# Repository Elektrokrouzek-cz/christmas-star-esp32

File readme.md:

# Christmas star with ESP32
This is the construction of ESP32-C3 based Christmas star.

There are also code examples written in MicroPython.

PCB is 2-layer and was designed using KiCad 10. Fabrication output for JLCPCB is in 
gerber folder.

**Happy soldering!**

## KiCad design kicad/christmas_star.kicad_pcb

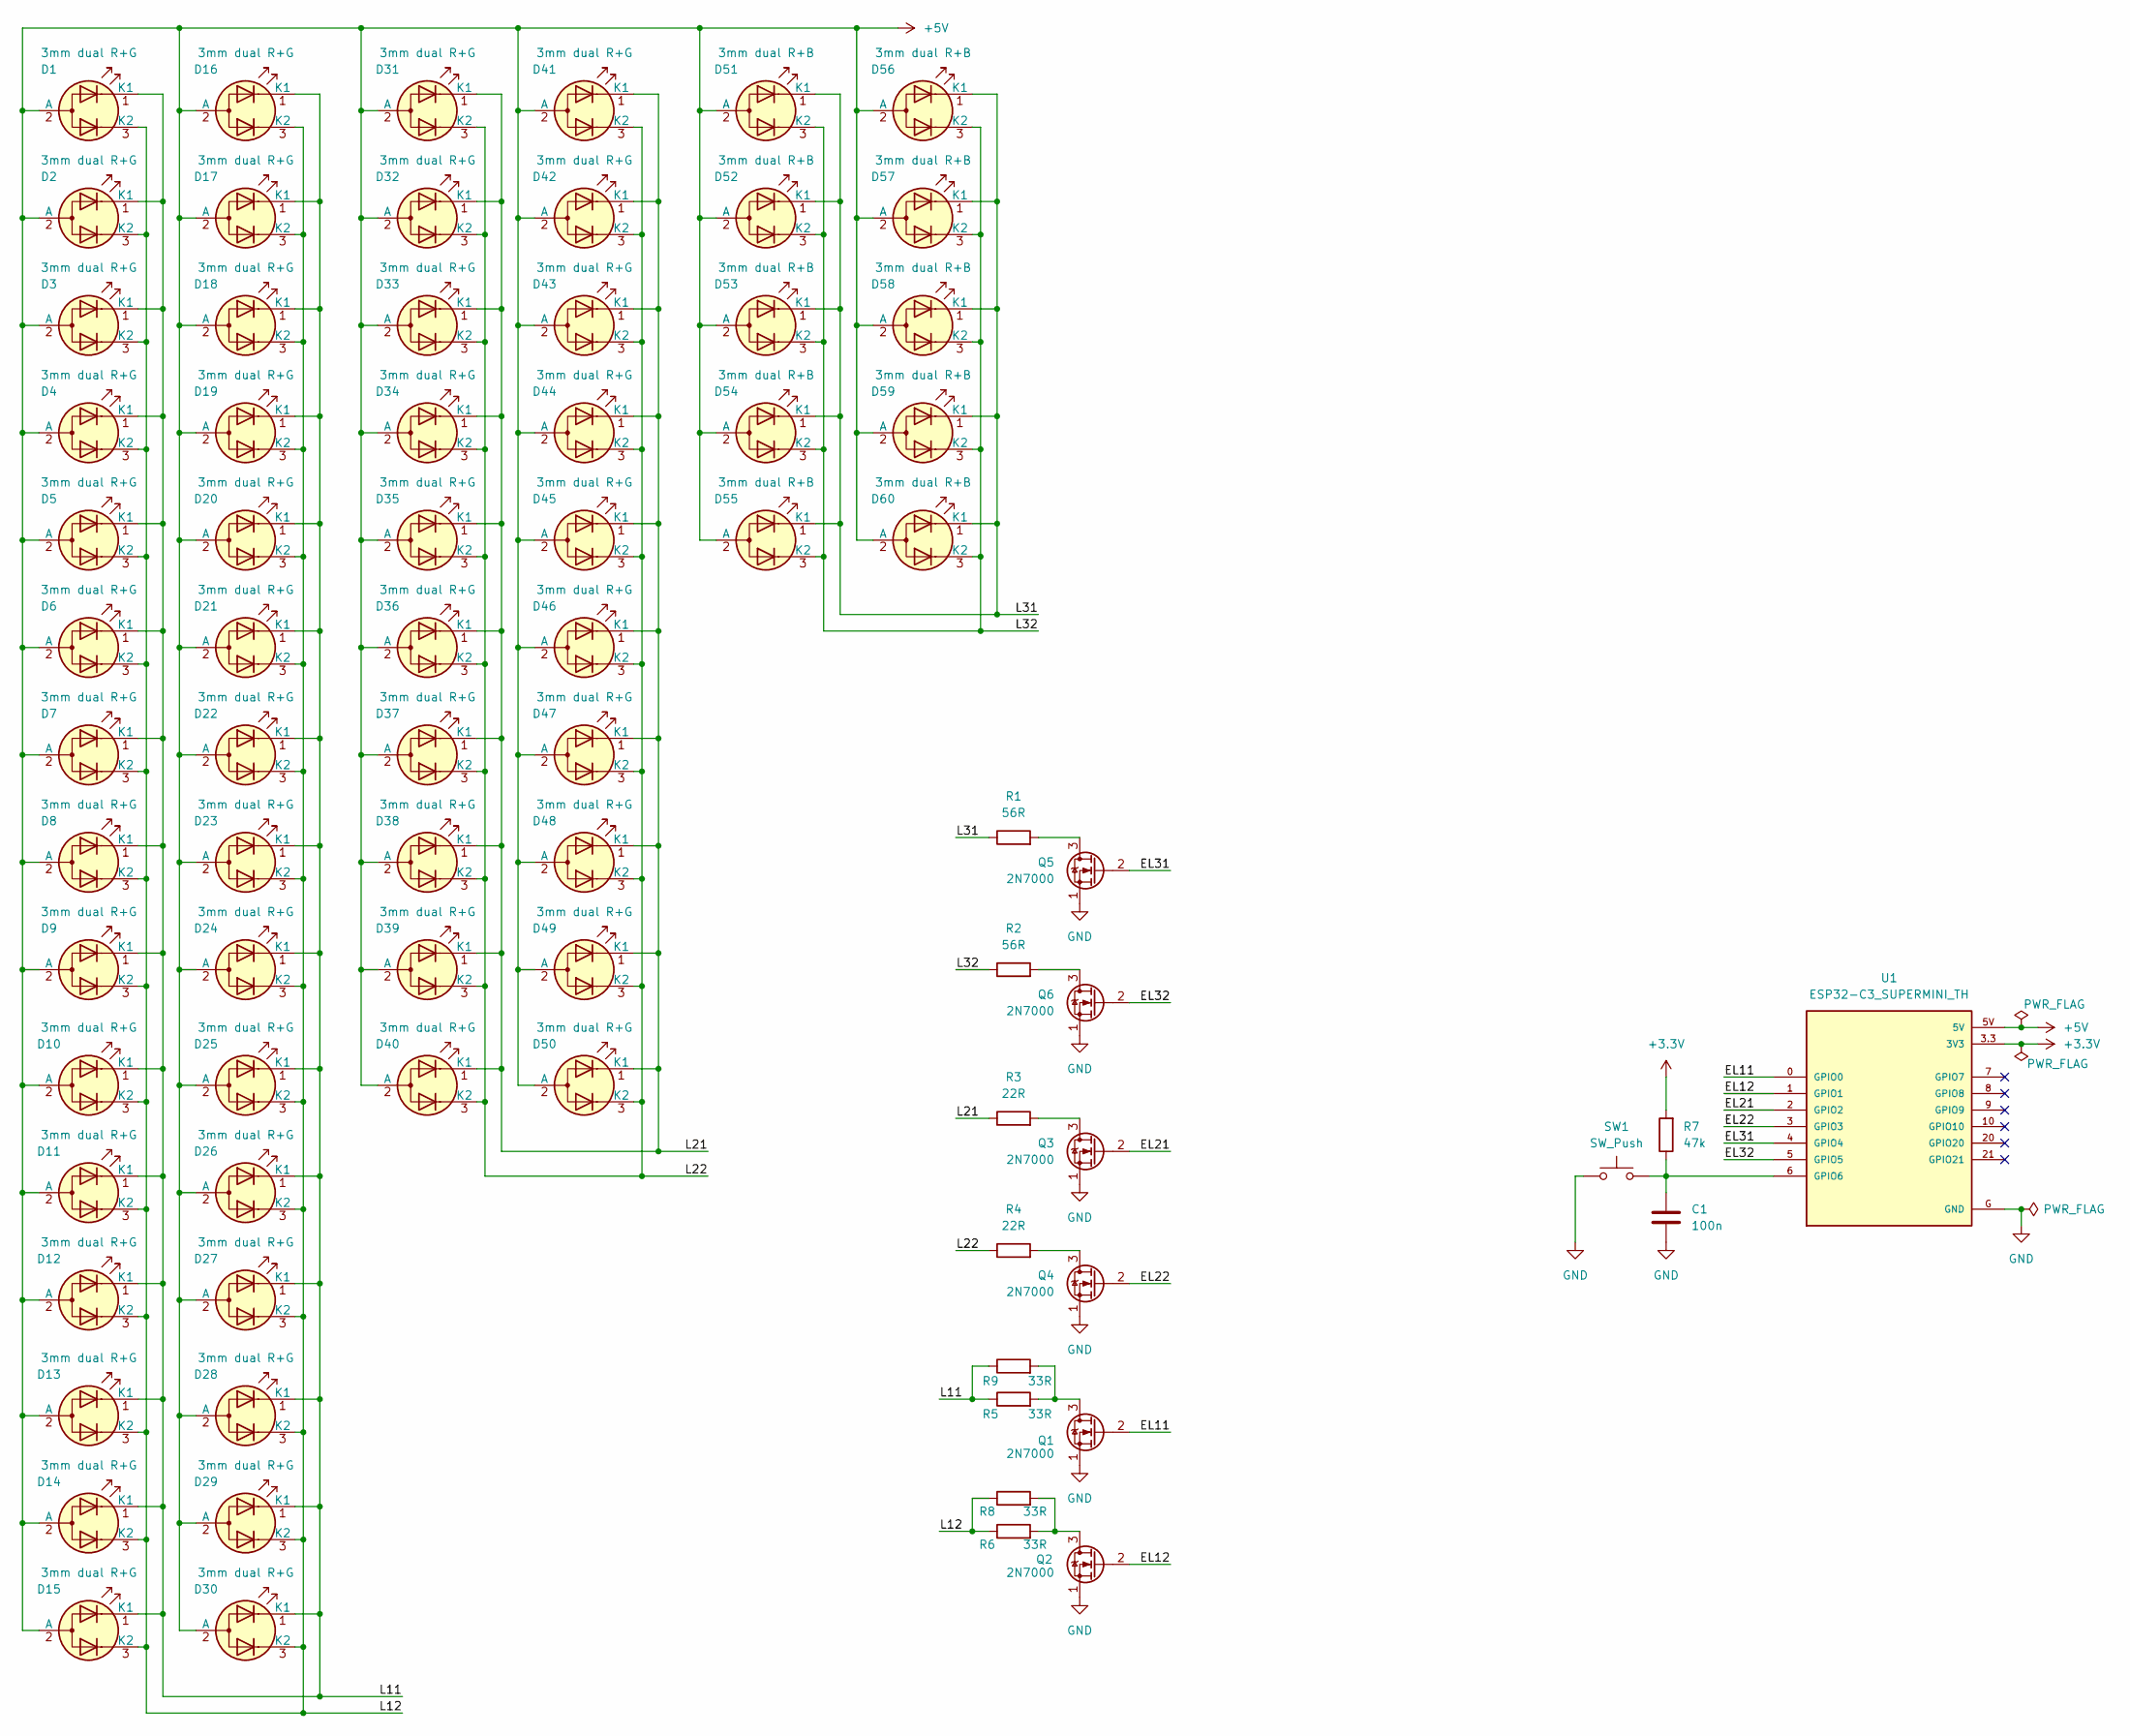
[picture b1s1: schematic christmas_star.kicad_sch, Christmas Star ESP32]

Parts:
C1: 100n; C_Disc_D5.0mm_W2.5mm_P5.00mm
D1, D2, D3, D4, D5, D6, D7, D8, D9, D10, D11, D12, D13, D14, D15, D16, D17, D18, D19, D20, D21, D22, D23, D24, D25, D26, D27, D28, D29, D30, D31, D32, D33, D34, D35, D36, D37, D38, D39, D40, D41, D42, D43, D44, D45, D46, D47, D48, D49, D50: 3mm dual R+G; LED_D3.0mm-3
D51, D52, D53, D54, D55, D56, D57, D58, D59, D60: 3mm dual R+B; LED_D3.0mm-3
Q1, Q2, Q3, Q4, Q5, Q6: 2N7000; TO-92_Inline_Wide
R1, R2: 56R; R_Axial_DIN0207_L6.3mm_D2.5mm_P7.62mm_Horizontal
R3, R4: 22R; R_Axial_DIN0207_L6.3mm_D2.5mm_P7.62mm_Horizontal
R5, R6, R8, R9: 33R; R_Axial_DIN0207_L6.3mm_D2.5mm_P7.62mm_Horizontal
R7: 47k; R_Axial_DIN0207_L6.3mm_D2.5mm_P7.62mm_Horizontal
SW1: SW_Push; SW_PUSH_6mm_H13mm
U1: ESP32-C3_SUPERMINI_TH; MODULE_ESP32-C3_SUPERMINI

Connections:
+3.3V: R7.2, U1.3.3 (3V3)
+5V: D1.2 (A), D2.2 (A), D3.2 (A), D4.2 (A), D5.2 (A), D6.2 (A), D7.2 (A), D8.2 (A), D9.2 (A), D10.2 (A), D11.2 (A), D12.2 (A), D13.2 (A), D14.2 (A), D15.2 (A), D16.2 (A), D17.2 (A), D18.2 (A), D19.2 (A), D20.2 (A), D21.2 (A), D22.2 (A), D23.2 (A), D24.2 (A), D25.2 (A), D26.2 (A), D27.2 (A), D28.2 (A), D29.2 (A), D30.2 (A), D31.2 (A), D32.2 (A), D33.2 (A), D34.2 (A), D35.2 (A), D36.2 (A), D37.2 (A), D38.2 (A), D39.2 (A), D40.2 (A), D41.2 (A), D42.2 (A), D43.2 (A), D44.2 (A), D45.2 (A), D46.2 (A), D47.2 (A), D48.2 (A), D49.2 (A), D50.2 (A), D51.2 (A), D52.2 (A), D53.2 (A), D54.2 (A), D55.2 (A), D56.2 (A), D57.2 (A), D58.2 (A), D59.2 (A), D60.2 (A), U1.5V
/EL11: Q1.2 (G), U1.0 (GPIO0)
/EL12: Q2.2 (G), U1.1 (GPIO1)
/EL21: Q3.2 (G), U1.2 (GPIO2)
/EL22: Q4.2 (G), U1.3 (GPIO3)
/EL31: Q5.2 (G), U1.4 (GPIO4)
/EL32: Q6.2 (G), U1.5 (GPIO5)
/L11: D1.1 (K1), D2.1 (K1), D3.1 (K1), D4.1 (K1), D5.1 (K1), D6.1 (K1), D7.1 (K1), D8.1 (K1), D9.1 (K1), D10.1 (K1), D11.1 (K1), D12.1 (K1), D13.1 (K1), D14.1 (K1), D15.1 (K1), D16.1 (K1), D17.1 (K1), D18.1 (K1), D19.1 (K1), D20.1 (K1), D21.1 (K1), D22.1 (K1), D23.1 (K1), D24.1 (K1), D25.1 (K1), D26.1 (K1), D27.1 (K1), D28.1 (K1), D29.1 (K1), D30.1 (K1), R5.1, R9.1
/L12: D1.3 (K2), D2.3 (K2), D3.3 (K2), D4.3 (K2), D5.3 (K2), D6.3 (K2), D7.3 (K2), D8.3 (K2), D9.3 (K2), D10.3 (K2), D11.3 (K2), D12.3 (K2), D13.3 (K2), D14.3 (K2), D15.3 (K2), D16.3 (K2), D17.3 (K2), D18.3 (K2), D19.3 (K2), D20.3 (K2), D21.3 (K2), D22.3 (K2), D23.3 (K2), D24.3 (K2), D25.3 (K2), D26.3 (K2), D27.3 (K2), D28.3 (K2), D29.3 (K2), D30.3 (K2), R6.1, R8.1
/L21: D31.1 (K1), D32.1 (K1), D33.1 (K1), D34.1 (K1), D35.1 (K1), D36.1 (K1), D37.1 (K1), D38.1 (K1), D39.1 (K1), D40.1 (K1), D41.1 (K1), D42.1 (K1), D43.1 (K1), D44.1 (K1), D45.1 (K1), D46.1 (K1), D47.1 (K1), D48.1 (K1), D49.1 (K1), D50.1 (K1), R3.1
/L22: D31.3 (K2), D32.3 (K2), D33.3 (K2), D34.3 (K2), D35.3 (K2), D36.3 (K2), D37.3 (K2), D38.3 (K2), D39.3 (K2), D40.3 (K2), D41.3 (K2), D42.3 (K2), D43.3 (K2), D44.3 (K2), D45.3 (K2), D46.3 (K2), D47.3 (K2), D48.3 (K2), D49.3 (K2), D50.3 (K2), R4.1
/L31: D51.1 (K1), D52.1 (K1), D53.1 (K1), D54.1 (K1), D55.1 (K1), D56.1 (K1), D57.1 (K1), D58.1 (K1), D59.1 (K1), D60.1 (K1), R1.1
/L32: D51.3 (K2), D52.3 (K2), D53.3 (K2), D54.3 (K2), D55.3 (K2), D56.3 (K2), D57.3 (K2), D58.3 (K2), D59.3 (K2), D60.3 (K2), R2.1
GND: C1.2, Q1.1 (S), Q2.1 (S), Q3.1 (S), Q4.1 (S), Q5.1 (S), Q6.1 (S), SW1.1, U1.G (GND)
unnamed: Q1.3 (D), R5.2, R9.2
unnamed: Q2.3 (D), R6.2, R8.2
unnamed: Q3.3 (D), R3.2
unnamed: Q4.3 (D), R4.2
unnamed: Q5.3 (D), R1.2
unnamed: Q6.3 (D), R2.2
unnamed: C1.1, R7.1, SW1.2, U1.6 (GPIO6)

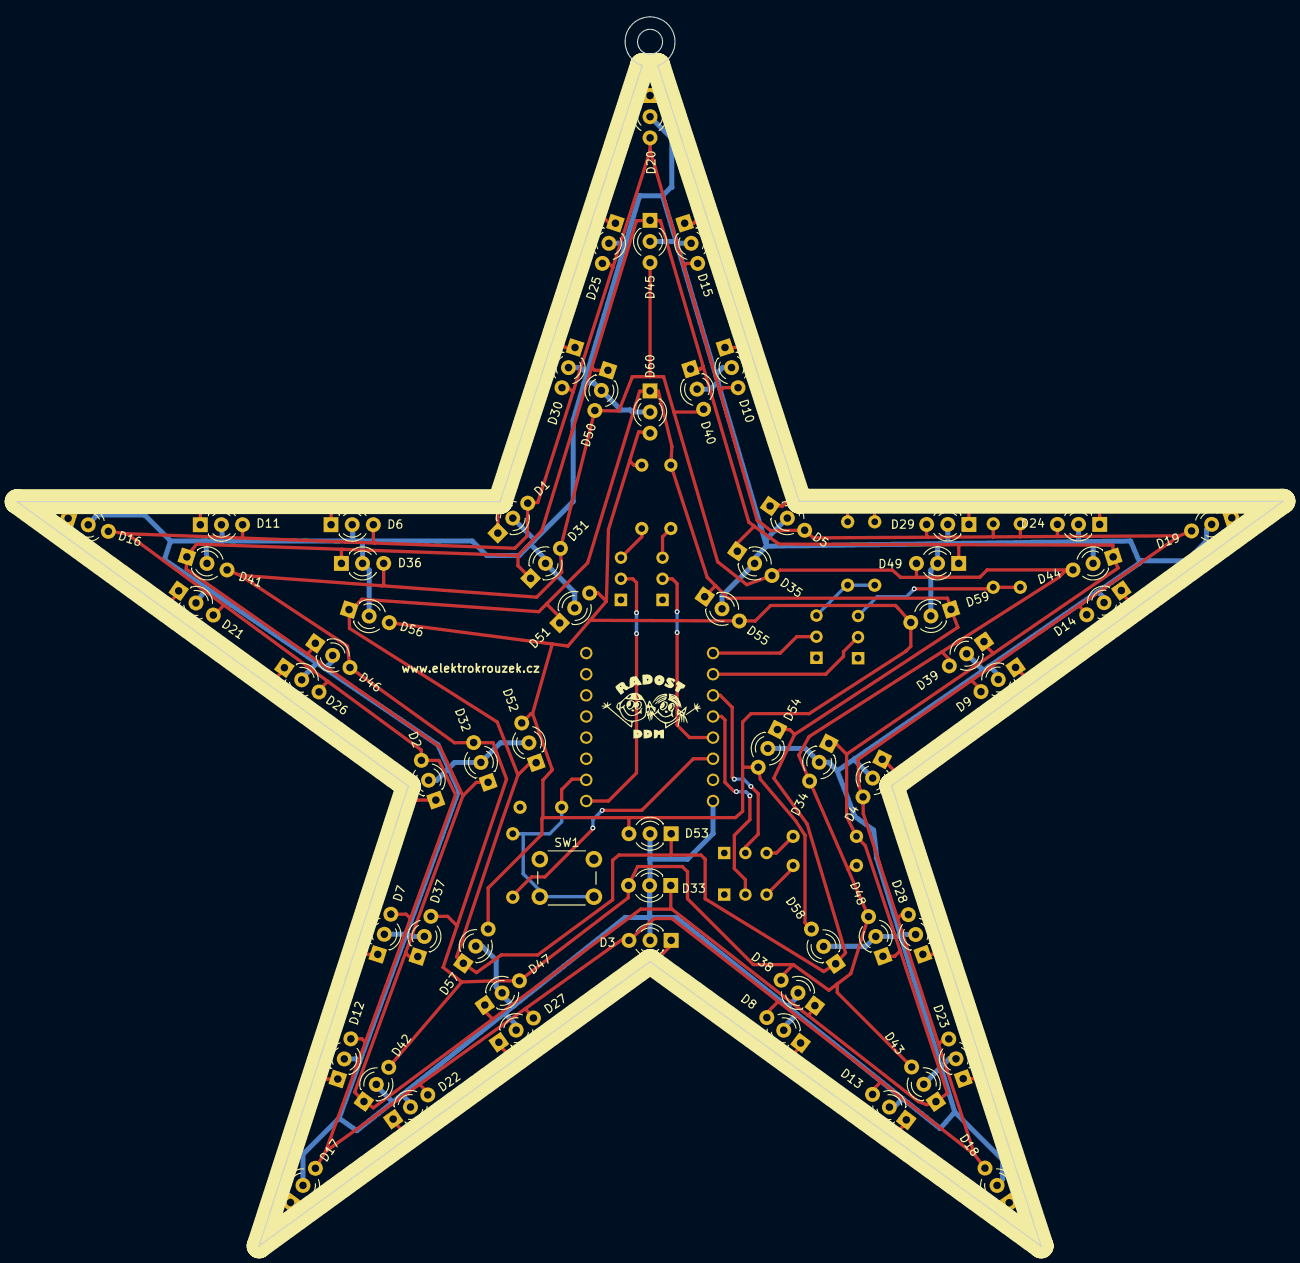
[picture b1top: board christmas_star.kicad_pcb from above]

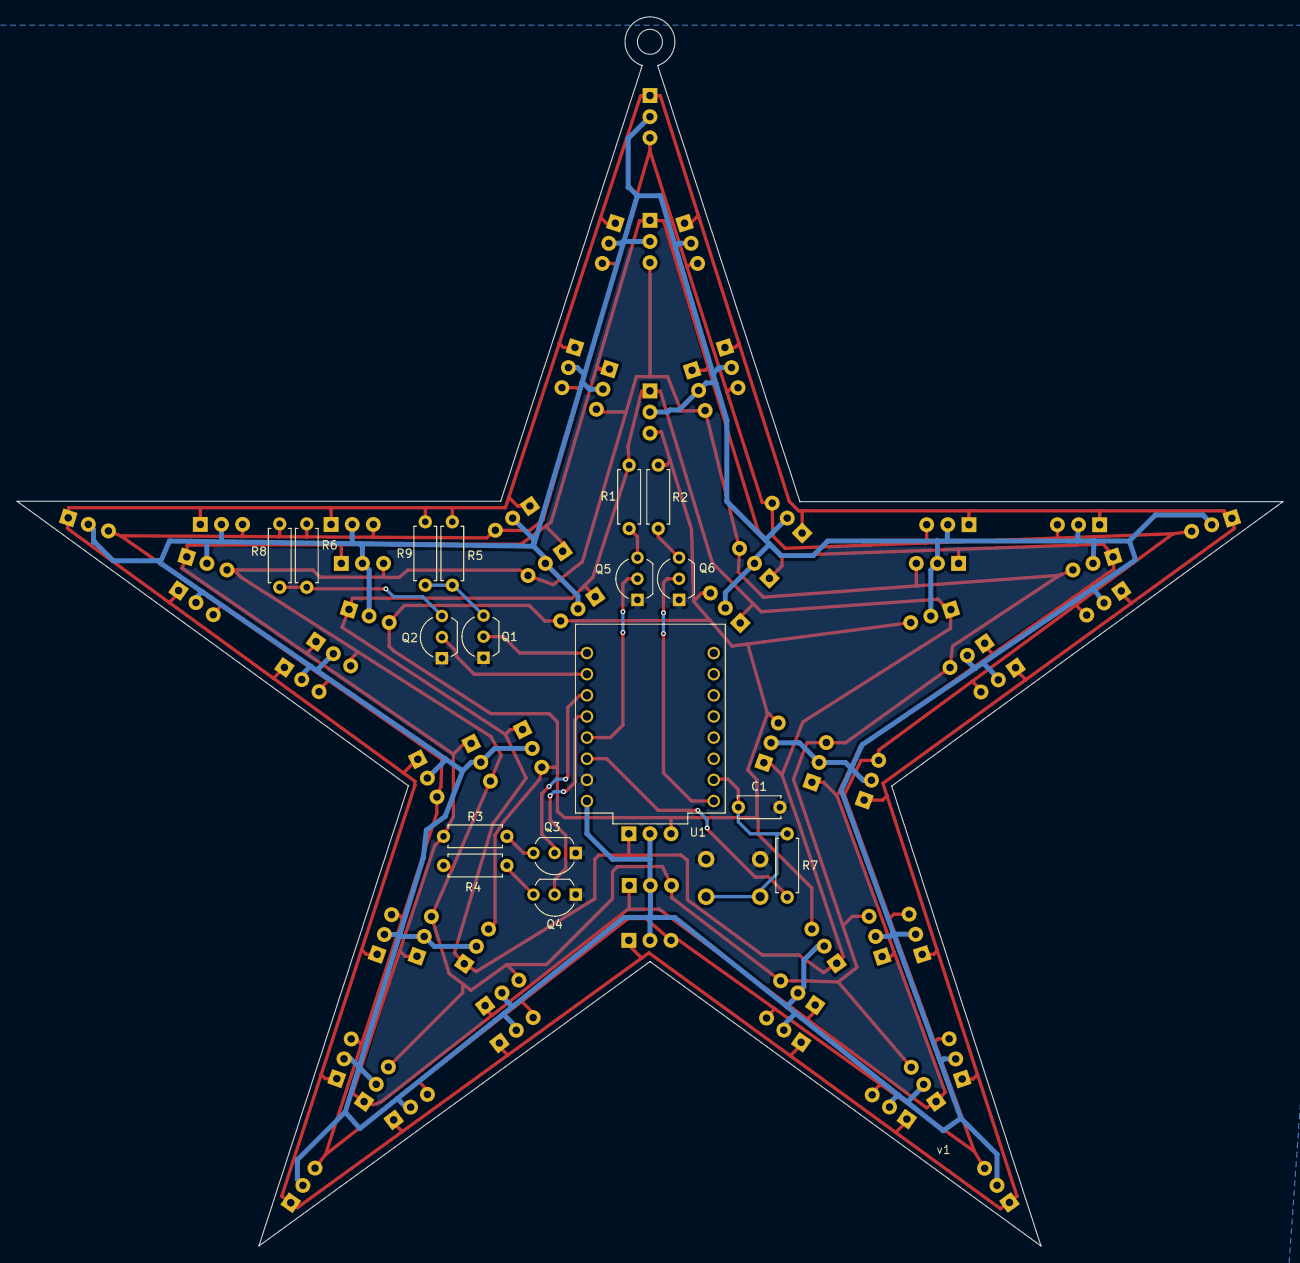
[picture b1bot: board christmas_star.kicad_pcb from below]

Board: 2 copper layers, 152.2 x 147.7 mm, 78 parts (17 on the bottom side), 22 nets.

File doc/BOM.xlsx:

Reference | Qty | Value | Footprint
C1 | 1 | 100n | Capacitor_THT:C_Disc_D5.0mm_W2.5mm_P5.00mm
D1,D2,D3,D4,D5,D6,D7,D8,D9,D10,D11,D12,D13,D14,D15,D16,D17,D18,D19,D20,D21,D22,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 | 50 | 3mm dual R+G | LED_THT:LED_D3.0mm-3
D51,D52,D53,D54,D55,D56,D57,D58,D59,D60 | 10 | 3mm dual R+B | LED_THT:LED_D3.0mm-3
Q1,Q2,Q3,Q4,Q5,Q6 | 6 | 2N7000 | Package_TO_SOT_THT:TO-92_Inline_Wide
R1,R2 | 2 | 56R | Resistor_THT:R_Axial_DIN0207_L6.3mm_D2.5mm_P7.62mm_Horizontal
R3,R4 | 2 | 22R | Resistor_THT:R_Axial_DIN0207_L6.3mm_D2.5mm_P7.62mm_Horizontal
R5,R6,R8,R9 | 4 | 33R | Resistor_THT:R_Axial_DIN0207_L6.3mm_D2.5mm_P7.62mm_Horizontal
R7 | 1 | 47k | Resistor_THT:R_Axial_DIN0207_L6.3mm_D2.5mm_P7.62mm_Horizontal
SW1 | 1 | SW_Push | Button_Switch_THT:SW_PUSH_6mm_H13mm
U1 | 1 | ESP32-C3_SUPERMINI_TH | ESP32-C3_SUPERMINI:MODULE_ESP32-C3_SUPERMINI
